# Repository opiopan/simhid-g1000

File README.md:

SimHID G1000
===

SimHID G1000 is a input device that imitates Garmin G1000 glass cockpit system for controlling flight simulators.<br>
This device is designed to utilize a iPad as a display.
iPad, iPad Air or iPad Pro with a display from 10.2 inches to 11 inches can be applied to this device.<br>

SimHID G1000 not only has 41 push buttons and 14 axes rotary encoders like the actual Garmin G1000,
but also has a total 6 input switches on both side of left and right sides.
These additional switches allow you to switch one device between PFD and MFD for both purposes.<br>

SimHID G1000 behaves as a USB virtual serial device, and communicate with the host using proprietary protocol named SimHID protocol.
In order to recognize this protocol and to control switching between PFD and MFD, I made a Windows application called [fsmapper](https://opiopan.github.io/fsmapper).

## How to build

The above image shows all parts that make up SimHID G1000.<br>
Most parts are 3D printed by FDM, but some parts are cut out and engraved from a 2mm thick acrylic plate using a laser cutter.
The model data for 3D printer and laser cutter are published at [Thingiverse](https://www.thingiverse.com/thing:4966493). Regarding these models, please refer [here](https://www.thingiverse.com/thing:4966493).

In this Github repository, PCB design and firmware source codes are hosted.<br>
Regarding PCB design related information include manufacturing, please refer README at [here](pcb/).<br>

Once all parts of SimHID G1000 are prepared, please assemble those according to [this procedure](docs/how-to-assemble.md).

**Note**: |
:----|
SimHID G1000 is entirely designed using [Fusion 360](https://www.autodesk.com/products/fusion-360/overview), including both mechanical and electrical components. If you want to modify the parts design, download [this Fusion 360 design file](https://raw.githubusercontent.com/wiki/opiopan/simhid-g1000/data/SimHID-G1000.f3d) and upload it to your Fusion 360 workspace.<br>Note that this file includes the 3D model of the PCB but does not contain the original netlist or artwork. The PCB design files are published separately [here](pcb), so upload them to Fusion 360 as well.

## Compatible iPad

SimHID G1000 uses an iPad as display. 
I assume that an iPad behave as second display of Windows PC by using an application such as [Duet Display](https://duetdisplay.com),
and show PFD or MFD images rendered by a flight simulator.<br>
An iPad can be easily inserted from the top of the SimHID G1000 along the guide like as the right image.<br>
I've confirmed to fit with SimHID G1000 only in case of iPad Air gen 3, 
but I believe that all iPad families with display from 10.2 inches to 11 inches can be fit.

The iPad list compatible with SimHID G1000 is below (as of Mar. 2026).

|Class | Model
|:----------:|------------------------------------|
|iPad Pro   | iPad Pro 10.5″<br>iPad Pro 11″ Gen 1<br>iPad Pro 11″ Gen 2<br>iPad Pro 11″ Gen 3<br>iPad Pro 11″ M4<br>iPad Pro 11″ M5
|iPad Air   | iPad Air Gen 3<br>iPad Air Gen 4<br>iPad Air Gen 5<br>iPad Air 11″ M2<br>iPad Air 11″ M3<br>iPad Air 11″ M4
|iPad       | iPad Gen 7<br>iPad Gen 8<br>iPad Gen 9<br>iPad Gen 10<br>iPad A16

## Compiling firmware
**Note**: |
:----|
The pre-built firmware can be downloaded from [here](https://github.com/opiopan/simhid-g1000/releases/latest/). If you haven’t modified the firmware code, using this version will be easier.

1. **Requirements**<br>
    Ensure that the [Arm GNU Toolchain](https://developer.arm.com/downloads/-/arm-gnu-toolchain-downloads) is installed and its bin folder is added to the `PATH` environment variable.
    Note that you need to install the toolchain for **AArch32 bare-metal** (`arm-none-eabi` variant).

    The Makefile for this firmware code is written with the assumption that it will be built in a Unix-like environment.
    If you are building on Windows, I strongly recommend using the Linux version of the Arm GNU Toolchain on WSL2.

2. **Downloading Source Codes**<br>
    ```shell
    $ git clone https://github.com/opiopan/simhid-g1000.git
    ```

3. **Compiling**
    ```shell
    $ cd simhid-g1000/firmware
    $ make all

## Programming Firmware
Once compiling as the above steps is done, following firmware binary files are made.
- ```firmware/build/simhid-g1000.elf``` : ELF format binary
- ```firmware/build/simhid-g1000.bin``` : raw binary

You can choose two way to program firmware to SimHID G1000.<br>
One is programming firmware via SWD by using debugger.  SimHID G1000 PCB exports a SWD I/F and you can access that from backside of this device.<br>
The other one is programming it via USB port in DFU mode. You can switch SimHID G1000 in DFU mode by inserting that to USB port with the button at right side pressed.

### Programming via Debugger
1. **Preparing Debugger**<br>
    Make sure that a debugger is connected with swd port (J6) and debugger controlling software which behave as GDB server such as OpenOCD is running.<br>
    Note that the J6 port does not have a power terminal, so you need to connect a USB port to supply power.

2. **Programming**<br>
    You can program a firmware by making ```flash``` target with ```DEBUGSERVER``` parameter.
    If debugger controlling software is running same PC, specify ```localhost``` for ```DEBUGSERVER``` parameter.

    ```shell
    $ make DEBUGSERVER=localhost flash
    ```
### Programming via USB

1. **Install required software**<br>
    Make sure that software with programming function via DFU is installed.
    Following softwares are populor to use for this purpose.
    - [STM32CubeMXProgrammer](https://www.st.com/ja/development-tools/stm32cubeprog.html)
    - [dfu-util](http://dfu-util.sourceforge.net)

2. **Switching SimHID G1000 in DFU mode**<br>
    Hold down the button on the right side of SimHID G1000 and connect that with USB port on PC.

3. **Programming**<br>
    In case using dfu-util, you can program just by making ```dfuflash``` target.

    ```shell
    $ make dfuflash
    ```

    Othrewise, follow the instructions for the software you are using.

4. **Exsiting from DFU mode**<br>
    Pull out SimHID G1000 from USB port on PC, then re-connect that to USB port.

## SimHID protocol
SimHID G1000 communicate with PC using a proprietary protocol named SimHID protocol via USB virtual serial port.<br>
Initially, I was considering that SimHID G1000 behaves as USB HID device which can be handled by Windows standard USB gaming controller device driver.
However in the end, I decided to implement a proprietary protocol because of two issues.<br>

One issue is distinguishability of each operable elements.<br>
SimHID G1000 consists of 47 binary switches (push buttons) and 14 axes rotary encoders. when each rotary encoders is expressed 2 push buttons, such as for clockwise and for counter clockwise, SimHID G1000 is recognized as a device that consists of 75 buttons. In case handling this device by the standard USB HID gaming controller device driver, all buttons are distinguished only by their serial number. For example, the push button on top of the rotary encoder for setting the navigation frequency is #12, the switch representing the left of joystick for map panning is #62.<br>
This situation is very complicated for me when I setting up the mappings between SimHID G1000 operation and aircraft control. 
I wanted to assign each operable elements a descriptive name.

The other one issue was actually based on my misunderstanding regarding rotary encoder performance.<br>
I estimated that multiple clicks by rotary encoder's rotation can occur during the communication interval with host. It means that click event may be dropped if each click event is expressed as a simple push button.<br>
So, I tried to express each axes of rotary encoder as a analog axis of USB gaming controller device.
However, I soon realized that this plan doesn't work because Windows standard USB gaming controller device driver limits the number of analog axes to a maximum of 8
even though there is no limit in the USB HID specification.<br>
In practice, only one click event occurs during the communication interval with host in normal usage, and there is no problem even if each rotation click event is expressed as push button down and up event.<br>

In summary, I decided to design a new proprietary protocol and implement that due to the former issue.

SimHID protocol is designed to be both human readable and machine readable.
You can observe communication data between a SimHID device and a host by using general terminal emulation software with serial port connectivity such as screen command.<br>
All commands to the device, responses from the device, and asynchronous events occurred by device operation are expressed one line text ending with end of line mark. The end of line mark consists combination of CR and LF, in other words, ```0Dh``` and ```0Ah``` byte sequences or ```"\r\n"``` C string.

The following is a example of data sent from SimHID G1000 when the 100-feet unit altitude dial is rotated clockwise 3 clicks then rotated counterclockwise 2 clicks.
```
S EC4X 1
S EC4X 1
S EC4X 1
S EC4X -1
S EC4X -1
```

The following is a case of pushing the MENU button then releasing it.
```
S SW28 1
S SW28 0
```

The above examples shows the cases of notification from the device to the host.
On the other hand, SimHID protocol also assumes tha cases that the host send data to a device in order to change status of a element of a device, such as turning on a LED.<br>
This upstream communication will be done by same format data, "```S <element-name> <value> \r\n```".

Regarding the details of SimHID protocol specification, please refer [this document](docs/simhid-protocol.md).

## Companion software
As mentioned above, I made a windows application, [fsmapper](https://opiopan.github.io/fsmapper), to control a flight simulator by using SimHID G1000.

fsmapper not only allows you to use the SimHID G1000 as a Garmin G1000, but it can also recreate virtual instrument panels for various aircraft on a touch display, and integrate common control devices such as joysticks and throttles.
For examples of operating various aircraft using fsmapper and the SimHID G1000 combination, refer to the following video.

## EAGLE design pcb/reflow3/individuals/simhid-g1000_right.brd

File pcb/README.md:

PCBs for SimHID G1000
===

> [!NOTE]
> SimHID G1000 was originally designed to use five [**ALPS EC11EBB24C03**](https://tech.alpsalpine.com/e/products/detail/EC11EBB24C03/) dual-shaft rotary encoders.
> This part was once discontinued (EOL) around 2022, but production and sales were resumed in 2025.<br/>
> As of now, [**EC11EBB24C03**](https://tech.alpsalpine.com/e/products/detail/EC11EBB24C03/) is marked as “**Not Recommended for New Designs**”, which means it is currently produced only to support existing designs, and its long-term availability is uncertain.
>
> For this reason, SimHID G1000 also supports [**BOURNS PEC11D-4120F-S0015**](https://www.bourns.com/products/encoders/contacting-encoders/product/PEC11D) as an alternative.
> This encoder is electrically and functionally compatible with the ALPS part, with the main difference being the shaft geometry.<br/>
> If you choose to use [**PEC11D-4120F-S0015**](https://www.bourns.com/products/encoders/contacting-encoders/product/PEC11D), please use [the alternative dual-shaft knob design provided here](https://www.thingiverse.com/thing:5804384).

The operable parts of SimHID G1000, the rotary encoders and push buttons, are distributed and mounted on three PCBs.<br>
The right board is the main board. The MCU [STM32F411CCU](https://www.st.com/en/microcontrollers-microprocessors/stm32f411cc.html) which is installed on the right board exports USB full speed PHY and communicate with PC via it.
That MCU also observes all operable components state via 16bits SPI I/O expanders, [MCP23S18-E/MJ](https://www.microchip.com/en-us/product/MCP23S18), on each PCB.<br>
Each PCB is connected with each other via 8-wire interconnect that consists 2 for power supply, 3 for SPI, and 3 for chip select.

I designed two variants of the PCB using [Autodesk Eagle](https://www.autodesk.com/products/eagle/overview) and same functions embedded in [Autodesk Fusion 360](https://www.autodesk.com/products/fusion-360/overview).
In the first variant, designed in March 2021, I used the [MCP23S18-E/MJ](https://www.microchip.com/en-us/product/MCP23S18) (QFN24) as the I/O expander. However, this component never made it to JLCPCB’s parts library.
At the time, with the chip shortage in full swing, other components were also out of stock, so I didn’t pay much attention to it. 
Now that the supply-demand situation for chips has improved, I decided to design a variant that uses components easier to manufacture with JLCPCB’s PCBA service. 
In the second variant, designed in September 2023, I replaced the MCP23S18-E/MJ with the [MCP23S17-E/ML](https://www.microchip.com/en-us/product/MCP23S17) (QFN28) and reduced the components mounted on the back of the PCB to only the Micro USB connector.

> [!NOTE]
> In late 2024, two additional PCB variants were designed primarily to improve the visual appearance of the device.  
> In the original design, the Micro USB connector is located on the right side of the PCB. Since the device must remain connected to a PC while in use, the USB cable is always visible, which the author personally found distracting.   
>
> The two new variants relocate the USB connector to the rear side of the PCB, allowing the cable to be routed out of sight.
> **Variant 3** uses a Micro USB connector, while **Variant 4** supports USB Type-C.
> 
> 3D-printable parts compatible with these rear-connector variants are also available for [download here](https://www.thingiverse.com/thing:7290593).

The design files of each PCB and the files required for manufacturing such as gerber files can be found below.

PCB Variant       | Eagle design files | Gerber files |BOM file| CPL file|Remarks
------------------|:-:|:-:|:-:|:-:|---
Variant 1|[handsoldering/individuals](handsoldering/individuals)|[PCB.zip](https://raw.githubusercontent.com/wiki/opiopan/simhid-g1000/data/allcomponents/PCB.zip)|[BOM.csv](https://raw.githubusercontent.com/wiki/opiopan/simhid-g1000/data/allcomponents/BOM.csv)|[CPL.csv](https://raw.githubusercontent.com/wiki/opiopan/simhid-g1000/data/allcomponents/CPL.csv)| Not recommended due to parts availability
Variant 2|[reflow/individuals](reflow/individuals)|[PCB_var2.zip](https://raw.githubusercontent.com/wiki/opiopan/simhid-g1000/data/allcomponents2/PCB_var2.zip)|[BOM_var2.csv](https://raw.githubusercontent.com/wiki/opiopan/simhid-g1000/data/allcomponents2/BOM_var2.csv)|[CPL_var2.csv](https://raw.githubusercontent.com/wiki/opiopan/simhid-g1000/data/allcomponents2/CPL_var2.csv)| Micro USB (right side)
Variant 3|[reflow2/individuals](reflow2/individuals)|[PCB_var3.zip](https://raw.githubusercontent.com/wiki/opiopan/simhid-g1000/data/allcomponents3/PCB_var3.zip)|[BOM_var3.csv](https://raw.githubusercontent.com/wiki/opiopan/simhid-g1000/data/allcomponents3/BOM_var3.csv)|[CPL_var3.csv](https://raw.githubusercontent.com/wiki/opiopan/simhid-g1000/data/allcomponents3/CPL_var3.csv)| Micro USB (rear)<br/>Requires the [different 3D-printed parts](https://www.thingiverse.com/thing:7290593)
Variant 4|[reflow3/individuals](reflow3/individuals)|[PCB_var4.zip](https://raw.githubusercontent.com/wiki/opiopan/simhid-g1000/data/allcomponents4/PCB_var4.zip)|[BOM_var4.csv](https://raw.githubusercontent.com/wiki/opiopan/simhid-g1000/data/allcomponents4/BOM_var4.csv)|[CPL_var4.csv](https://raw.githubusercontent.com/wiki/opiopan/simhid-g1000/data/allcomponents4/CPL_var4.csv)| USB Type-C (rear)<br/>Requires the [different 3D-printed parts](https://www.thingiverse.com/thing:7290593)

The PCB manufacturing files provided in the table — including the Gerber archive, BOM file, and CPL file — conform to [JLCPCB](https://jlcpcb.com/)’s rules and requirements.   
You can submit these files directly to the [JLCPCB PCB Assembly Service](https://cart.jlcpcb.com/quote) without modification.

When using the above file to manufacture the PCB at JLCPCB, specify the following parameters during production.

Parameter | Specification
----------|--------------
Different Design|3
PCB Thickness| 1.0 mm
Tooling holes| Added by Customer
PCBA Type /<br>Assembly Side|My recommendation is ***'Economic'*** for the ***'PCBA Type'*** and ***'Top Side'*** for the ***'Assembly Side'***.<br><br>When assembling components on both sides of the board, you must select ***'Standard'*** for the ***'PCBA Type'***. This results in a significant cost increase. For example, if you manufacture two units of Variant 2, selecting ***'Economic'*** and ***'Top Side'*** costs $188.07, whereas selecting ***'Standard'*** and ***'Both Side'*** increases the price to $270.25. That’s quite a large amount to pay for soldering just two Micro USB connectors, each costing only $0.34, isn’t it?<br><br>If you use the PCBA service to assemble only the top side, you’ll need to manually solder following parts on the bottom side yourself;<br/> - **Variant 1**: [MCP1703AT-3302E/CB](https://www.digikey.com/en/products/detail/microchip-technology/MCP1703AT-3302E-CB/3131472) and [ZX62-B-5PA(33)](https://www.hirose.com/en/product/p/CL0242-0033-8-33)<br/> - **Variant 2**: [ZX62-B-5PA(33)](https://www.hirose.com/en/product/p/CL0242-0033-8-33)<br/> - **Variant 3**: [1051330031](https://www.molex.com/en-us/products/part-detail/1051330031)<br/> - **Variant 4**: [USB4145](https://gct.co/connector/usb4145)

## Schematic Diagram

## BOM List
Components | Value / Product Number | Remarks
-----------|------------------------|------------------------------
U1, U2, U3, U5 | MCP23S18-E/MJ or MCP23S17-E/ML | 16bits SPI I/O expander
U4         | STM32F411CCU           |
U6         | MCP1703AT-3302E/CB     | SOT-23 LDO
J1         | **Var1/2**: Hirose ZX62-B-5PA(33)<br/>**Var3**: Molex 1051330031<br/>**Var4**: GCT USB4145  | Micro USB receptacle connector (Variant 1/2/3)<br/>USB Type-C receptacle connector (Variant 4)
J6         | MOLEX 53047-0410       | **OPTIONAL for debugging**<br>Firmware downloading can be proceeded by using DFU mode instead debugger
X1         | 16MHz Crystal (3225)   | load capacitance: 10pF
C1, C2, C3, C9, C10, C11, C12, C13, C14, C15, C17, C19, C20  | 0.1uF (0402)             |
C4, C5, C8 | 1uF (0402)           |
C6, C7     | 22pF (0402)            | need to change value if X1's load capacitance is not 10pF
C16, C18   | 4.7uF (0402)           |
R1, R2, R11, R12, R13, R14, R15, R16, R17,<br> R18, R19, R20, R21, R22, R23, R24, R25, R26,<br> R27, R28, R29, R30, R31, R32, R33, R34, R35,<br> R36, R37, R38, R39, R40, R41, R42, R43, R44,<br> R45, R46, R47, R48, R49, R50, R51, R52, R53, R54, R55, R56, R57, R58, R59| 10k ohm (0402)         |
R3, R4, R5, R6, R7, R8, R9, R10     | 10k ohm x 4 (0603 x 4) | 
R60, R61| 5.1K ohm (0402)| Applicable to Variant 4 only
SW1, SW27  | SLLB510100           |
SW2, SW3, SW4, SW5, SW6, SW7, SW8, <br>SW9, SW10, SW11, SW12, SW13, SW14,<br> SW15, SW16, SW17, SW18, SW19, SW20,<br> SW21, SW22, SW23, SW24, SW25, SW26,<br> SW28, SW29, SW30, SW31, SW32, SW33, SW34 | 4.5mm x 4.5mm tact switch | 4.3mm height
EC1, EC3, EC5 | EC12D1524403 | 1 axis rotary encoder with push button
EC2, EC4, EC6, EC7, EC9 | EC11EBB24C03 or PEC11D-4120F-S0015 | 2 axes rotary encoder with push button
EC8 | RKJXT1F42001 | 4 directional joystick with 1 axis rotary encoder and push button

## Supplement
### PCB interconnect
Each PCB are connected to adjacent PCB via the 8 pads junction for interconnect, that are J2, J3, J4 and J5.<br>
It is recommended to solder the interconnect with the PCBs fixed to the front housing of SimHID G1000 in order to properly adjust the length of the wires connecting between PCBs as below.

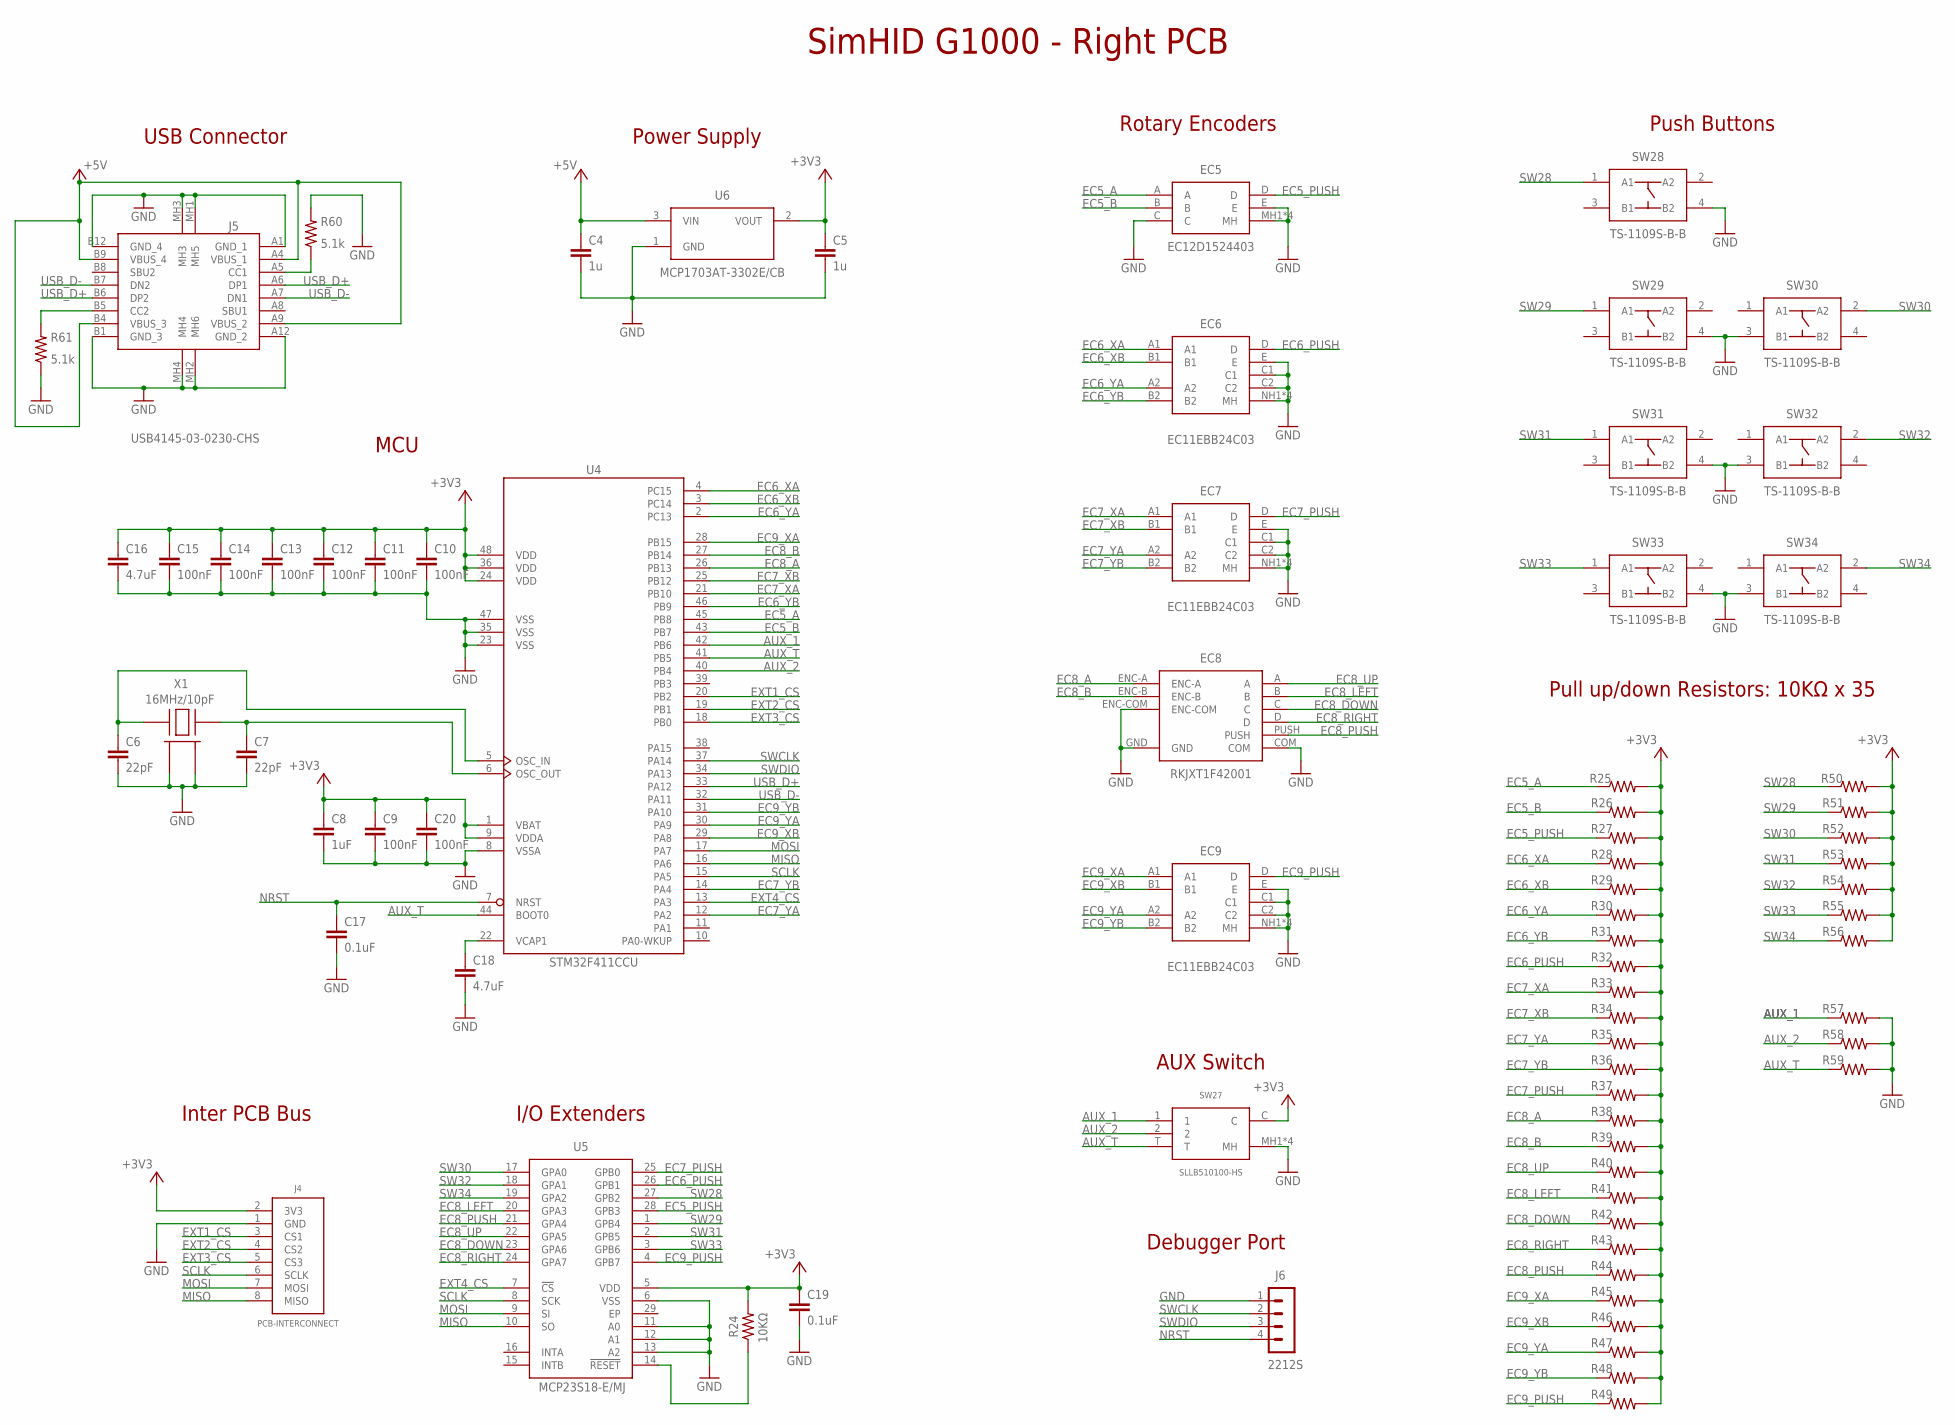
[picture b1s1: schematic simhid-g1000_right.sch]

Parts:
C4, C5: 1u; RCL_C0402_HS
C6, C7: 22pF; RCL_C0402_HS
C8: 1uF; RCL_C0402_HS
C9, C10, C11, C12, C13, C14, C15, C20: 100nF; RCL_C0402_HS
C16, C18: 4.7uF; RCL_C0402_HS
C17, C19: 0.1uF; RCL_C0402_HS
EC5: EC12D1524403
EC6, EC7, EC9: EC11EBB24C03
EC8: RKJXT1F42001
J4: PCB-INTERCONNECT
J5: USB4145-03-0230-CHS; USB4145030230C-HS
J6: 2212S; 53047-0410
R24: 10KΩ; RCL_R0402_HS
R25, R26, R27, R28, R29, R30, R31, R32, R33, R34, R35, R36, R37, R38, R39, R40, R41, R42, R43, R44, R45, R46, R47, R48, R49, R50, R51, R52, R53, R54, R55, R56, R57, R58, R59: RCL_R-US_R0402-HS; RCL_R0402_HS
R60, R61: 5.1k; RCL_R0402_HS
SW27: SLLB510100-HS
SW28, SW29, SW30, SW31, SW32, SW33, SW34: TS-1109S-B-B
U4: STM32F411CCU; UFQFPN48
U5: MCP23S18-E/MJ; QFN65P600X600X100-29N
U6: MCP1703AT-3302E/CB; SOT23
X1: 16MHz/10pF; CRYSTAL3225-HS

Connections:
+3V3: C5.1, C8.1, C9.1, C10.1, C11.1, C12.1, C13.1, C14.1, C15.1, C16.1, C19.1, C20.1, J4.2 (3V3), R24.2, R25.2, R26.2, R27.2, R28.2, R29.2, R30.2, R31.2, R32.2, R33.2, R34.2, R35.2, R36.2, R37.2, R38.2, R39.2, R40.2, R41.2, R42.2, R43.2, R44.2, R45.2, R46.2, R47.2, R48.2, R49.2, R50.2, R51.2, R52.2, R53.2, R54.2, R55.2, R56.2, SW27.C, U4.1 (VBAT), U4.9 (VDDA), U4.24 (VDD), U4.36 (VDD), U4.48 (VDD), U5.5 (VDD), U6.2 (VOUT)
+5V: C4.1, J5.A4 (VBUS_1), J5.A9 (VBUS_2), J5.B4 (VBUS_3), J5.B9 (VBUS_4), U6.3 (VIN)
AUX_1: R57.1, SW27.1, U4.42 (PB6)
AUX_2: R58.1, SW27.2, U4.40 (PB4)
AUX_T: R59.1, SW27.T, U4.41 (PB5), U4.44 (BOOT0)
EC5_A: EC5.A, R25.1, U4.45 (PB8)
EC5_B: EC5.B, R26.1, U4.43 (PB7)
EC5_PUSH: EC5.D, R27.1, U5.28 (GPB3)
EC6_PUSH: EC6.D, R32.1, U5.26 (GPB1)
EC6_XA: EC6.A1, R28.1, U4.4 (PC15)
EC6_XB: EC6.B1, R29.1, U4.3 (PC14)
EC6_YA: EC6.A2, R30.1, U4.2 (PC13)
EC6_YB: EC6.B2, R31.1, U4.46 (PB9)
EC7_PUSH: EC7.D, R37.1, U5.25 (GPB0)
EC7_XA: EC7.A1, R33.1, U4.21 (PB10)
EC7_XB: EC7.B1, R34.1, U4.25 (PB12)
EC7_YA: EC7.A2, R35.1, U4.12 (PA2)
EC7_YB: EC7.B2, R36.1, U4.14 (PA4)
EC8_A: EC8.ENC-A, R38.1, U4.26 (PB13)
EC8_B: EC8.ENC-B, R39.1, U4.27 (PB14)
EC8_DOWN: EC8.C, R42.1, U5.23 (GPA6)
EC8_LEFT: EC8.B, R41.1, U5.20 (GPA3)
EC8_PUSH: EC8.PUSH, R44.1, U5.21 (GPA4)
EC8_RIGHT: EC8.D, R43.1, U5.24 (GPA7)
EC8_UP: EC8.A, R40.1, U5.22 (GPA5)
EC9_PUSH: EC9.D, R49.1, U5.4 (GPB7)
EC9_XA: EC9.A1, R45.1, U4.28 (PB15)
EC9_XB: EC9.B1, R46.1, U4.29 (PA8)
EC9_YA: EC9.A2, R47.1, U4.30 (PA9)
EC9_YB: EC9.B2, R48.1, U4.31 (PA10)
EXT1_CS: J4.3 (CS1), U4.20 (PB2)
EXT2_CS: J4.4 (CS2), U4.19 (PB1)
EXT3_CS: J4.5 (CS3), U4.18 (PB0)
EXT4_CS: U4.13 (PA3), U5.7 (!CS)
GND: C4.2, C5.2, C6.2, C7.2, C8.2, C9.2, C10.2, C11.2, C12.2, C13.2, C14.2, C15.2, C16.2, C17.2, C18.2, C19.2, C20.2, EC5.C, EC5.E, EC5.MH1 (MH), EC5.MH2 (MH), EC5.MH3 (MH), EC5.MH4 (MH), EC6.C1, EC6.C2, EC6.E, EC6.NH1 (MH), EC6.NH2 (MH), EC6.NH3 (MH), EC6.NH4 (MH), EC7.C1, EC7.C2, EC7.E, EC7.NH1 (MH), EC7.NH2 (MH), EC7.NH3 (MH), EC7.NH4 (MH), EC8.COM, EC8.ENC-COM, EC8.GND, EC9.C1, EC9.C2, EC9.E, EC9.NH1 (MH), EC9.NH2 (MH), EC9.NH3 (MH), EC9.NH4 (MH), J4.1 (GND), J5.A1 (GND_1), J5.A12 (GND_2), J5.B1 (GND_3), J5.B12 (GND_4), J5.MH1 (MH5), J5.MH2 (MH6), J5.MH3, J5.MH4, J6.1, R57.2, R58.2, R59.2, R60.2, R61.1, SW27.MH1 (MH), SW27.MH2 (MH), SW27.MH3 (MH), SW27.MH4 (MH), SW28.4 (B2), SW29.4 (B2), SW30.3 (B1), SW31.4 (B2), SW32.3 (B1), SW33.4 (B2), SW34.3 (B1), U4.8 (VSSA), U4.23 (VSS), U4.35 (VSS), U4.47 (VSS), U5.6 (VSS), U5.11 (A0), U5.12 (A1), U5.13 (A2), U6.1 (GND), X1.2 (GND_1), X1.4 (GND_2)
MISO: J4.8 (MISO), U4.16 (PA6), U5.10 (SO)
MOSI: J4.7 (MOSI), U4.17 (PA7), U5.9 (SI)
unnamed: R24.1, U5.14 (!RESET)
unnamed: J5.A5 (CC1), R60.1
unnamed: J5.B5 (CC2), R61.2
NRST: C17.1, J6.4, U4.7 (NRST)
OSC_IN: C6.1, U4.5 (OSC_IN), X1.1 (HOT_1)
OSC_OUT: C7.1, U4.6 (OSC_OUT), X1.3 (HOT_2)
SCLK: J4.6 (SCLK), U4.15 (PA5), U5.8 (SCK)
SW28: R50.1, SW28.1 (A1), U5.27 (GPB2)
SW29: R51.1, SW29.1 (A1), U5.1 (GPB4)
SW30: R52.1, SW30.2 (A2), U5.17 (GPA0)
SW31: R53.1, SW31.1 (A1), U5.2 (GPB5)
SW32: R54.1, SW32.2 (A2), U5.18 (GPA1)
SW33: R55.1, SW33.1 (A1), U5.3 (GPB6)
SW34: R56.1, SW34.2 (A2), U5.19 (GPA2)
SWCLK: J6.2, U4.37 (PA14)
SWDIO: J6.3, U4.34 (PA13)
USB_D+: J5.A6 (DP1), J5.B6 (DP2), U4.33 (PA12)
USB_D-: J5.A7 (DN1), J5.B7 (DN2), U4.32 (PA11)
VCAP: C18.1, U4.22 (VCAP1)

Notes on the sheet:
USB Connector
Power Supply
MCU
Debugger Port
Inter PCB Bus
I/O Extenders
Rotary Encoders
AUX Switch
Push Buttons
Pull up/down Resistors: 10KΩ x 35
SimHID G1000 - Right PCB

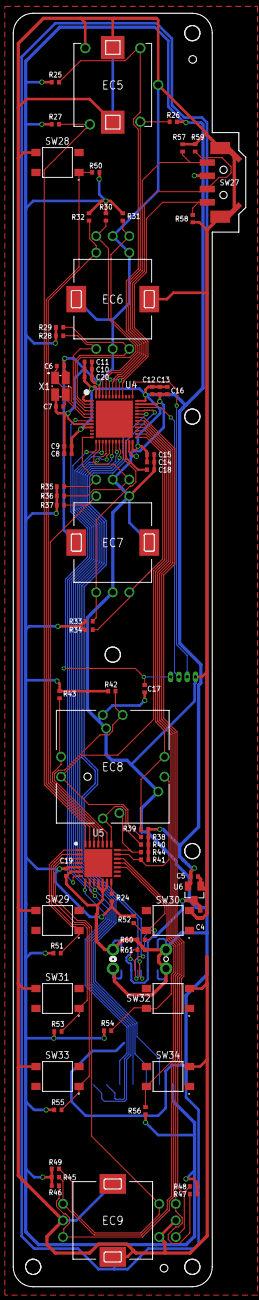
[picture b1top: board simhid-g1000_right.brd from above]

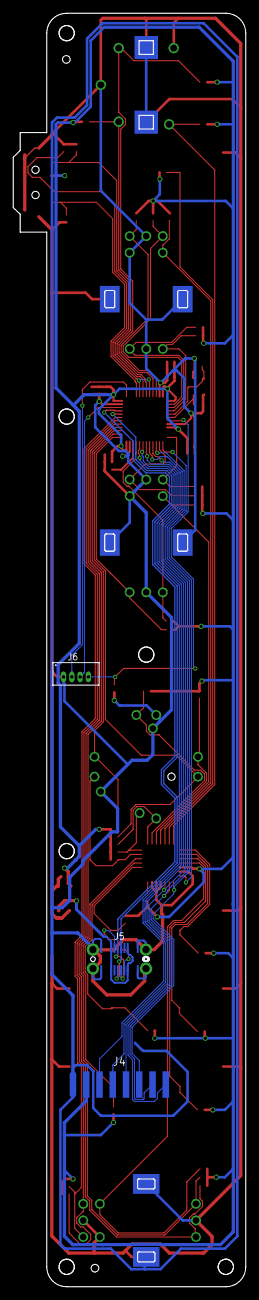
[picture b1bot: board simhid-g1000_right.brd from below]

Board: 2 copper layers, 35.0 x 192.0 mm, 75 parts (3 on the bottom side), 56 nets.

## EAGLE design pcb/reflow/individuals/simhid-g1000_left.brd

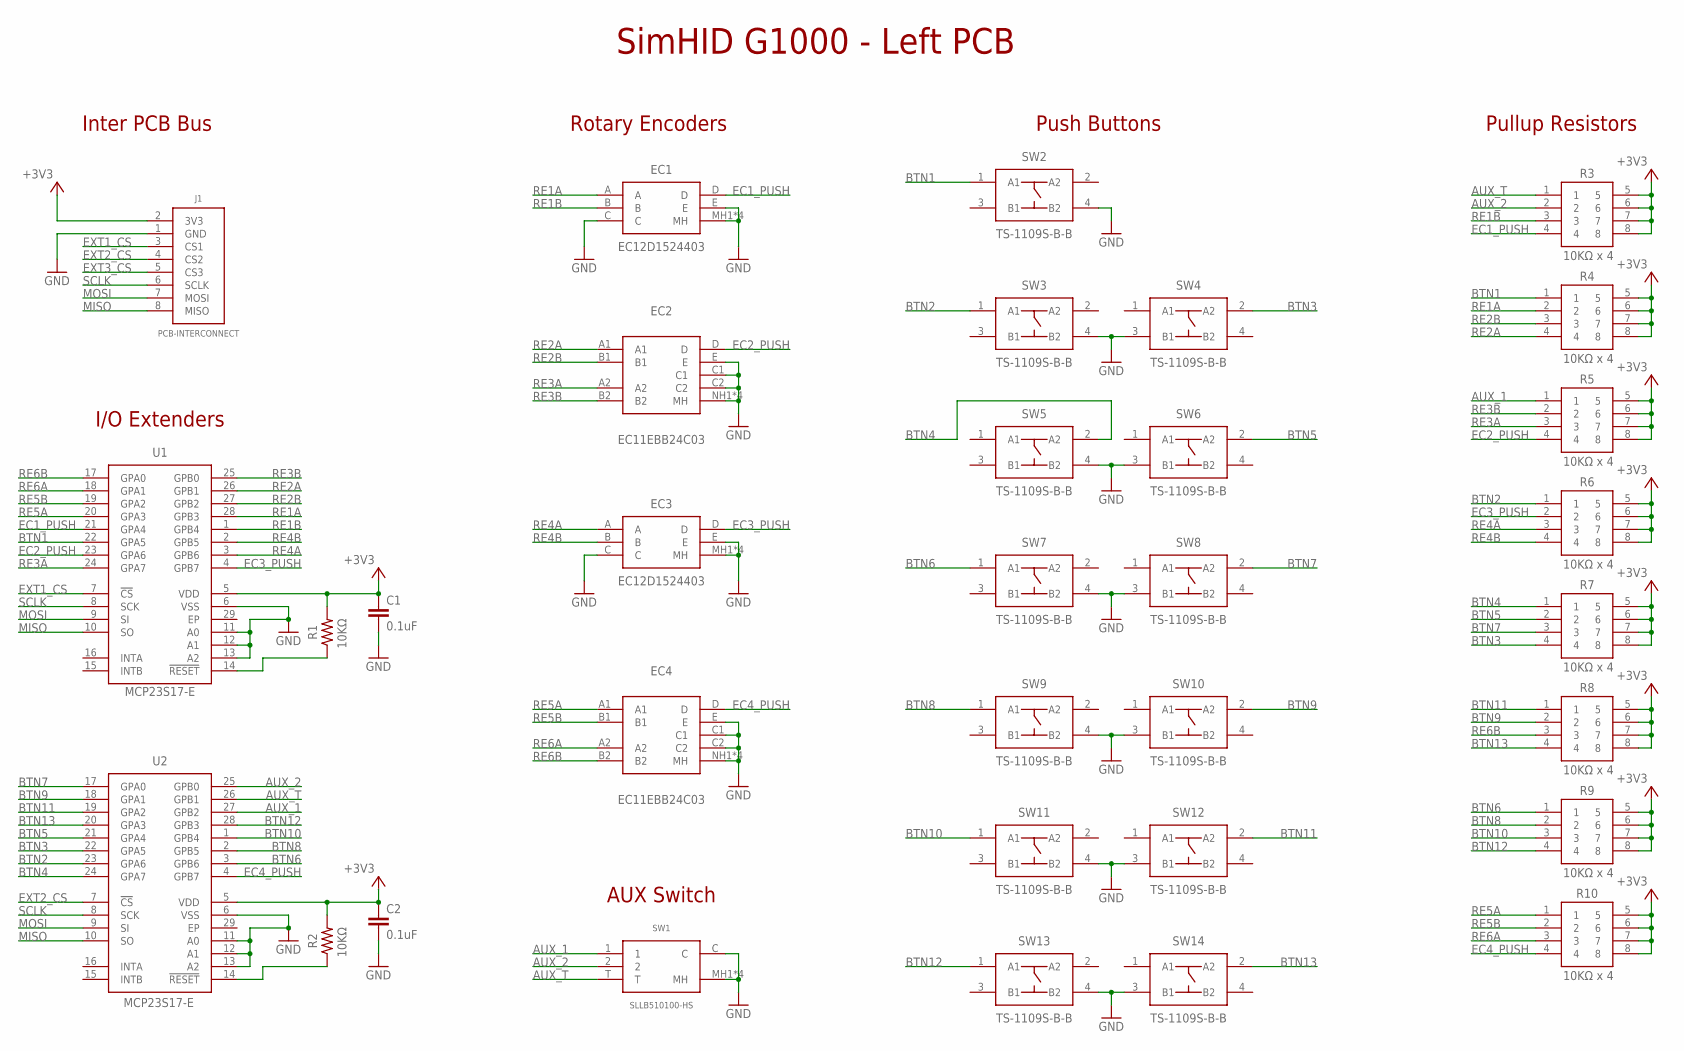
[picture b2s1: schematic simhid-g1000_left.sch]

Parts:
C1, C2: 0.1uF; RCL_C0402_HS
EC1, EC3: EC12D1524403
EC2, EC4: EC11EBB24C03
J1: PCB-INTERCONNECT
R1, R2: 10KΩ; RCL_R0402_HS
R3, R4, R5, R6, R7, R8, R9, R10: 10KΩ x 4; BCN164A_1
SW1: SLLB510100-HS
SW2, SW3, SW4, SW5, SW6, SW7, SW8, SW9, SW10, SW11, SW12, SW13, SW14: TS-1109S-B-B
U1, U2: MCP23S17-E; QFN65P600X600X100-29N

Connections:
+3V3: C1.1, C2.1, J1.2 (3V3), R1.2, R2.2, R3.5, R3.6, R3.7, R3.8, R4.5, R4.6, R4.7, R4.8, R5.5, R5.6, R5.7, R5.8, R6.5, R6.6, R6.7, R6.8, R7.5, R7.6, R7.7, R7.8, R8.5, R8.6, R8.7, R8.8, R9.5, R9.6, R9.7, R9.8, R10.5, R10.6, R10.7, R10.8, U1.5 (VDD), U2.5 (VDD)
AUX_1: R5.1, SW1.1, U2.27 (GPB2)
AUX_2: R3.2, SW1.2, U2.25 (GPB0)
AUX_T: R3.1, SW1.T, U2.26 (GPB1)
BTN1: R4.1, SW2.1 (A1), U1.22 (GPA5)
BTN2: R6.1, SW3.1 (A1), U2.23 (GPA6)
BTN3: R7.4, SW4.2 (A2), U2.22 (GPA5)
BTN4: R7.1, SW5.2 (A2), U2.24 (GPA7)
BTN5: R7.2, SW6.2 (A2), U2.21 (GPA4)
BTN6: R9.1, SW7.1 (A1), U2.3 (GPB6)
BTN7: R7.3, SW8.2 (A2), U2.17 (GPA0)
BTN8: R9.2, SW9.1 (A1), U2.2 (GPB5)
BTN9: R8.2, SW10.2 (A2), U2.18 (GPA1)
BTN10: R9.3, SW11.1 (A1), U2.1 (GPB4)
BTN11: R8.1, SW12.2 (A2), U2.19 (GPA2)
BTN12: R9.4, SW13.1 (A1), U2.28 (GPB3)
BTN13: R8.4, SW14.2 (A2), U2.20 (GPA3)
EC1_PUSH: EC1.D, R3.4, U1.21 (GPA4)
EC2_PUSH: EC2.D, R5.4, U1.23 (GPA6)
EC3_PUSH: EC3.D, R6.2, U1.4 (GPB7)
EC4_PUSH: EC4.D, R10.4, U2.4 (GPB7)
EXT1_CS: J1.3 (CS1), U1.7 (!CS)
EXT2_CS: J1.4 (CS2), U2.7 (!CS)
EXT3_CS: J1.5 (CS3)
GND: C1.2, C2.2, EC1.C, EC1.E, EC1.MH1 (MH), EC1.MH2 (MH), EC1.MH3 (MH), EC1.MH4 (MH), EC2.C1, EC2.C2, EC2.E, EC2.NH1 (MH), EC2.NH2 (MH), EC2.NH3 (MH), EC2.NH4 (MH), EC3.C, EC3.E, EC3.MH1 (MH), EC3.MH2 (MH), EC3.MH3 (MH), EC3.MH4 (MH), EC4.C1, EC4.C2, EC4.E, EC4.NH1 (MH), EC4.NH2 (MH), EC4.NH3 (MH), EC4.NH4 (MH), J1.1 (GND), SW1.C, SW1.MH1 (MH), SW1.MH2 (MH), SW1.MH3 (MH), SW1.MH4 (MH), SW2.4 (B2), SW3.4 (B2), SW4.3 (B1), SW5.4 (B2), SW6.3 (B1), SW7.4 (B2), SW8.3 (B1), SW9.4 (B2), SW10.3 (B1), SW11.4 (B2), SW12.3 (B1), SW13.4 (B2), SW14.3 (B1), U1.6 (VSS), U1.11 (A0), U1.12 (A1), U1.13 (A2), U2.6 (VSS), U2.11 (A0), U2.12 (A1), U2.13 (A2)
MISO: J1.8 (MISO), U1.10 (SO), U2.10 (SO)
MOSI: J1.7 (MOSI), U1.9 (SI), U2.9 (SI)
unnamed: R1.1, U1.14 (!RESET)
unnamed: R2.1, U2.14 (!RESET)
RE1A: EC1.A, R4.2, U1.28 (GPB3)
RE1B: EC1.B, R3.3, U1.1 (GPB4)
RE2A: EC2.A1, R4.4, U1.26 (GPB1)
RE2B: EC2.B1, R4.3, U1.27 (GPB2)
RE3A: EC2.A2, R5.3, U1.24 (GPA7)
RE3B: EC2.B2, R5.2, U1.25 (GPB0)
RE4A: EC3.A, R6.3, U1.3 (GPB6)
RE4B: EC3.B, R6.4, U1.2 (GPB5)
RE5A: EC4.A1, R10.1, U1.20 (GPA3)
RE5B: EC4.B1, R10.2, U1.19 (GPA2)
RE6A: EC4.A2, R10.3, U1.18 (GPA1)
RE6B: EC4.B2, R8.3, U1.17 (GPA0)
SCLK: J1.6 (SCLK), U1.8 (SCK), U2.8 (SCK)

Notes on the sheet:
Inter PCB Bus
I/O Extenders
Rotary Encoders
AUX Switch
Push Buttons
SimHID G1000 - Left PCB
Pullup Resistors

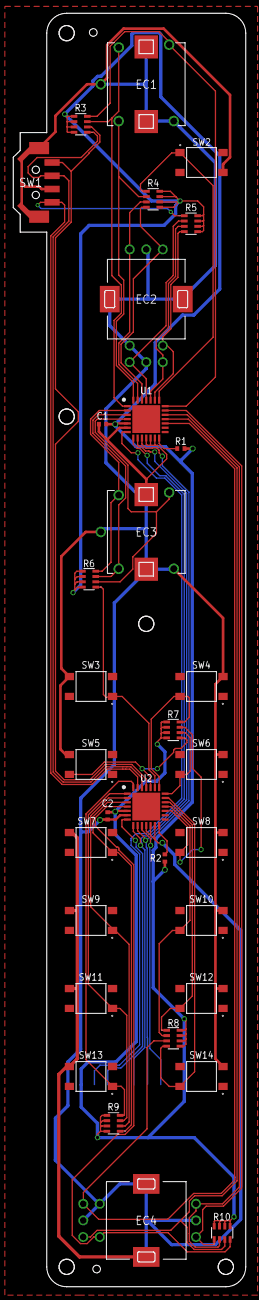
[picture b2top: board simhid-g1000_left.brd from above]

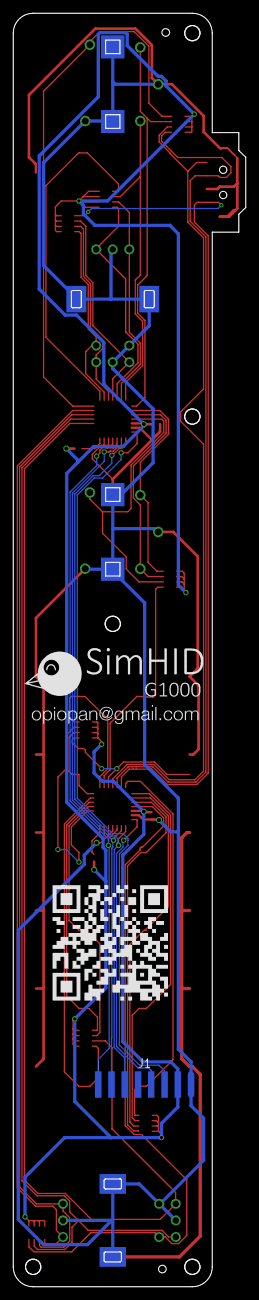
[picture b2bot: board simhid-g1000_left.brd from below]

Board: 2 copper layers, 35.0 x 192.0 mm, 35 parts (3 on the bottom side), 41 nets.

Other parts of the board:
U$1: SHIMHID-G1000-QRCODE
U$2: SIMHID-G1000-LOGO

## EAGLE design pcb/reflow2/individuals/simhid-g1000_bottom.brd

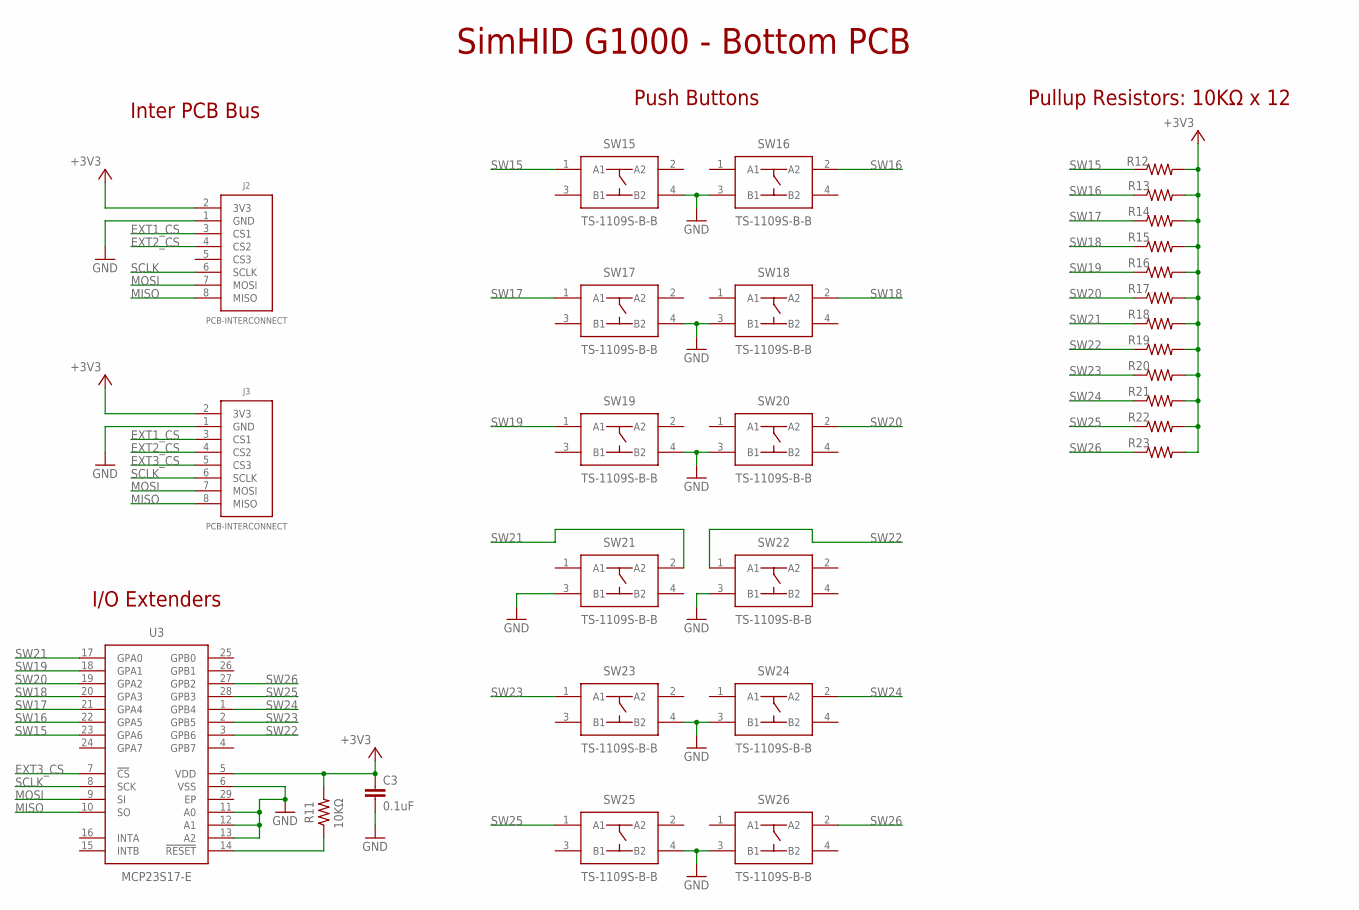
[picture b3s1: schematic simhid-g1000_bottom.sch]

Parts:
C3: 0.1uF; RCL_C0402_HS
J2, J3: PCB-INTERCONNECT
R11: 10KΩ; RCL_R0402_HS
R12, R13, R14, R15, R16, R17, R18, R19, R20, R21, R22, R23: RCL_R-US_R0402-HS; RCL_R0402_HS
SW15, SW16, SW17, SW18, SW19, SW20, SW21, SW22, SW23, SW24, SW25, SW26: TS-1109S-B-B
U3: MCP23S17-E; QFN65P600X600X100-29N

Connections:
+3V3: C3.1, J2.2 (3V3), J3.2 (3V3), R11.2, R12.2, R13.2, R14.2, R15.2, R16.2, R17.2, R18.2, R19.2, R20.2, R21.2, R22.2, R23.2, U3.5 (VDD)
EXT1_CS: J2.3 (CS1), J3.3 (CS1)
EXT2_CS: J2.4 (CS2), J3.4 (CS2)
EXT3_CS: J3.5 (CS3), U3.7 (!CS)
GND: C3.2, J2.1 (GND), J3.1 (GND), SW15.4 (B2), SW16.3 (B1), SW17.4 (B2), SW18.3 (B1), SW19.4 (B2), SW20.3 (B1), SW21.3 (B1), SW22.3 (B1), SW23.4 (B2), SW24.3 (B1), SW25.4 (B2), SW26.3 (B1), U3.6 (VSS), U3.11 (A0), U3.12 (A1), U3.13 (A2)
MISO: J2.8 (MISO), J3.8 (MISO), U3.10 (SO)
MOSI: J2.7 (MOSI), J3.7 (MOSI), U3.9 (SI)
RESET: R11.1, U3.14 (!RESET)
SCLK: J2.6 (SCLK), J3.6 (SCLK), U3.8 (SCK)
SW15: R12.1, SW15.1 (A1), U3.23 (GPA6)
SW16: R13.1, SW16.2 (A2), U3.22 (GPA5)
SW17: R14.1, SW17.1 (A1), U3.21 (GPA4)
SW18: R15.1, SW18.2 (A2), U3.20 (GPA3)
SW19: R16.1, SW19.1 (A1), U3.18 (GPA1)
SW20: R17.1, SW20.2 (A2), U3.19 (GPA2)
SW21: R18.1, SW21.2 (A2), U3.17 (GPA0)
SW22: R19.1, SW22.1 (A1), U3.3 (GPB6)
SW23: R20.1, SW23.1 (A1), U3.2 (GPB5)
SW24: R21.1, SW24.2 (A2), U3.1 (GPB4)
SW25: R22.1, SW25.1 (A1), U3.28 (GPB3)
SW26: R23.1, SW26.2 (A2), U3.27 (GPB2)

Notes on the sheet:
Inter PCB Bus
I/O Extenders
Push Buttons
Pullup Resistors: 10KΩ x 12
SimHID G1000 - Bottom PCB

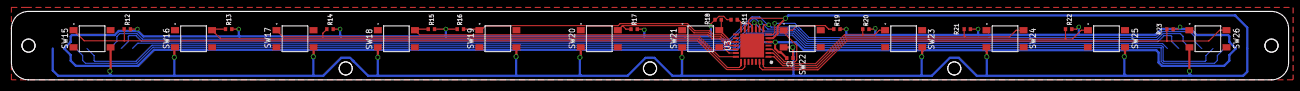
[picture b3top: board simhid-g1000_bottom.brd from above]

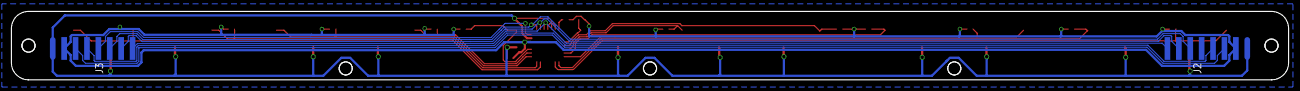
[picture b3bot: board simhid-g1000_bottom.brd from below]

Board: 2 copper layers, 224.0 x 12.0 mm, 29 parts (2 on the bottom side), 21 nets.

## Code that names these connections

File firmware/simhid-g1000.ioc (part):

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Mcu.Name=STM32F411C(C-E)Ux
Mcu.Package=UFQFPN48
Mcu.UserName=STM32F411CEUx
PA10.GPIOParameters=GPIO_Label
PA10.GPIO_Label=EC9YB
PA10.Signal=GPIO_Input
PA11.Mode=Device_Only
PA11.Signal=USB_OTG_FS_DM
PA12.Mode=Device_Only
PA12.Signal=USB_OTG_FS_DP
PA13.Mode=Serial_Wire
PA13.Signal=SYS_JTMS-SWDIO
PA14.Mode=Serial_Wire
PA14.Signal=SYS_JTCK-SWCLK
PA2.GPIOParameters=GPIO_Label
PA2.GPIO_Label=EC7YA
PA2.Signal=GPIO_Input
PA3.GPIOParameters=PinState,GPIO_Label
PA3.GPIO_Label=EXT4CS
PA3.PinState=GPIO_PIN_SET
PA3.Signal=GPIO_Output
PA4.GPIOParameters=GPIO_Label
PA4.GPIO_Label=EC7YB
PA4.Signal=GPIO_Input
PA5.Mode=Full_Duplex_Master
PA5.Signal=SPI1_SCK
PA6.Mode=Full_Duplex_Master
PA6.Signal=SPI1_MISO
PA7.Mode=Full_Duplex_Master
PA7.Signal=SPI1_MOSI
PA8.GPIOParameters=GPIO_Label
PA8.GPIO_Label=EC9XB
PA8.Signal=GPIO_Input
PA9.GPIOParameters=GPIO_Label
PA9.GPIO_Label=EC9YA
PA9.Signal=GPIO_Input
PB0.GPIOParameters=PinState,GPIO_Label
PB0.GPIO_Label=EXT3CS
PB0.PinState=GPIO_PIN_SET
PB0.Signal=GPIO_Output
PB1.GPIOParameters=PinState,GPIO_Label
PB1.GPIO_Label=EXT2CS
PB1.PinState=GPIO_PIN_SET
PB1.Signal=GPIO_Output
PB10.GPIOParameters=GPIO_Label
PB10.GPIO_Label=EC7XA
PB10.Signal=GPIO_Input
PB12.GPIOParameters=GPIO_Label
PB12.GPIO_Label=EC7XB
PB12.Signal=GPIO_Input
PB13.GPIOParameters=GPIO_Label
PB13.GPIO_Label=EC8A
PB13.Signal=GPIO_Input
PB14.GPIOParameters=GPIO_Label
PB14.GPIO_Label=EC8B
PB14.Signal=GPIO_Input
PB15.GPIOParameters=GPIO_Label
PB15.GPIO_Label=EC9XA
PB15.Signal=GPIO_Input
PB2.GPIOParameters=PinState,GPIO_Label
PB2.GPIO_Label=EXT1CS
PB2.PinState=GPIO_PIN_SET
PB2.Signal=GPIO_Output
PB4.GPIOParameters=GPIO_Label
PB4.GPIO_Label=AUX2D
PB4.Signal=GPIO_Input
PB5.GPIOParameters=GPIO_Label
PB5.GPIO_Label=AUX2P
PB5.Signal=GPIO_Input
PB6.GPIOParameters=GPIO_Label
PB6.GPIO_Label=AUX2U
PB6.Signal=GPIO_Input
PB7.GPIOParameters=GPIO_Label
PB7.GPIO_Label=EC5B
PB7.Signal=GPIO_Input
PB8.GPIOParameters=GPIO_Label
PB8.GPIO_Label=EC5A
PB8.Signal=GPIO_Input
PB9.GPIOParameters=GPIO_Label
PB9.GPIO_Label=EC6YB
PB9.Signal=GPIO_Input
PC13-ANTI_TAMP.GPIOParameters=GPIO_Label
PC13-ANTI_TAMP.GPIO_Label=EC6YA
PC13-ANTI_TAMP.Signal=GPIO_Input
PC14-OSC32_IN.GPIOParameters=GPIO_Label
PC14-OSC32_IN.GPIO_Label=EC6XB
PC14-OSC32_IN.Signal=GPIO_Input
PC15-OSC32_OUT.GPIOParameters=GPIO_Label
PC15-OSC32_OUT.GPIO_Label=EC6XA
PC15-OSC32_OUT.Signal=GPIO_Input
PH0\ -\ OSC_IN.Mode=HSE-External-Oscillator
PH0\ -\ OSC_IN.Signal=RCC_OSC_IN
PH1\ -\ OSC_OUT.Mode=HSE-External-Oscillator
PH1\ -\ OSC_OUT.Signal=RCC_OSC_OUT
RCC.HSE_VALUE=16000000
RCC.SYSCLKFreq_VALUE=96000000
RCC.SYSCLKSource=RCC_SYSCLKSOURCE_PLLCLK
board=custom

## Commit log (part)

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2021-04-29 basic switch scanning fuction has been implemented
2021-04-29 modify filter function for RKJXT1F42001 to handle raw data as negative logic
2021-04-30 fix a issue of filter for RKJXT1F42001
2021-05-04 add basic host communication protocol
2021-05-09 added command parser and executer
2021-05-10 fix a parser issue
2021-05-10 add a command to retrieve switch definitions
2021-05-12 add option command
2021-05-12 add automatically firmware version embedding fanctionality
2021-06-20 refactoring
2021-09-16 add docmuments
2021-09-17 improve assemble procedure
2021-09-20 fix the issue that LPF for button input is not work
2021-09-20 add a moview on README.md
2021-09-22 remove unnecessary files
2021-09-24 add debugging messsages
2021-09-25 fix a issue that hungup after resume PC
2021-12-20 add BIT result in the response of I command
2021-12-29 fix a issue that building firmware is failed when gcc version is 10 or later
2021-12-29 fix a issue that firmwre building is failed at first time after clone the github repository
2021-12-29 code refactoring
2023-01-22 added information regarding installing PEC11D-4120F-20015 instead of EC11EBB24C03
2023-09-22 Added non-divisible PCB artwork with the goal of reducing manufacturing costs
2023-09-25 Added vertical USB connector versions
2023-10-09 revised pcb design for reflow
2024-04-20 fix a issue of documentation
2024-10-05 updated the documentation
2024-12-20 Fixes #7
2024-12-21 updated README to note how to build the firmware on Windows
2024-12-31 added a PCB variant
2025-01-11 improved Makefile to address the problem reported in issue #8
2025-01-11 improved the artwork for the new variant
2025-02-16 added a note to the README indicating that power supply via the USB port is required when programming the firmware via SWD
2025-06-26 added the parameter ‘B’ to the 'I' command to output BIT results
2025-07-12 modified the behavior so that initialization of MCP23S1* is retried once upon failure (issue #10)
2025-09-06 Fix incorrect initialization parameters for MCP23S17 / MCP23S18 I misread the datasheet and misunderstood the effect of the IOCON register’s SEQOP bit. To enable Sequential Operation Mode, the SEQOP 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
2026-02-07 Modify the PCB design for USB Type-C
2026-02-07 Minor chages of the PCB design for USB Type-C
2026-02-08 Update a README
2026-02-08 Fix a minor issue
2026-02-09 Modified the README to describe PCB variant 3 and variant 4
2026-02-09 Fix a link issue on README
2026-02-09 Improve the description for the PCB variants
2026-02-09 Update the README
2026-02-20 update the BOM for the variant 4 to correct the type-c connector footprint id
